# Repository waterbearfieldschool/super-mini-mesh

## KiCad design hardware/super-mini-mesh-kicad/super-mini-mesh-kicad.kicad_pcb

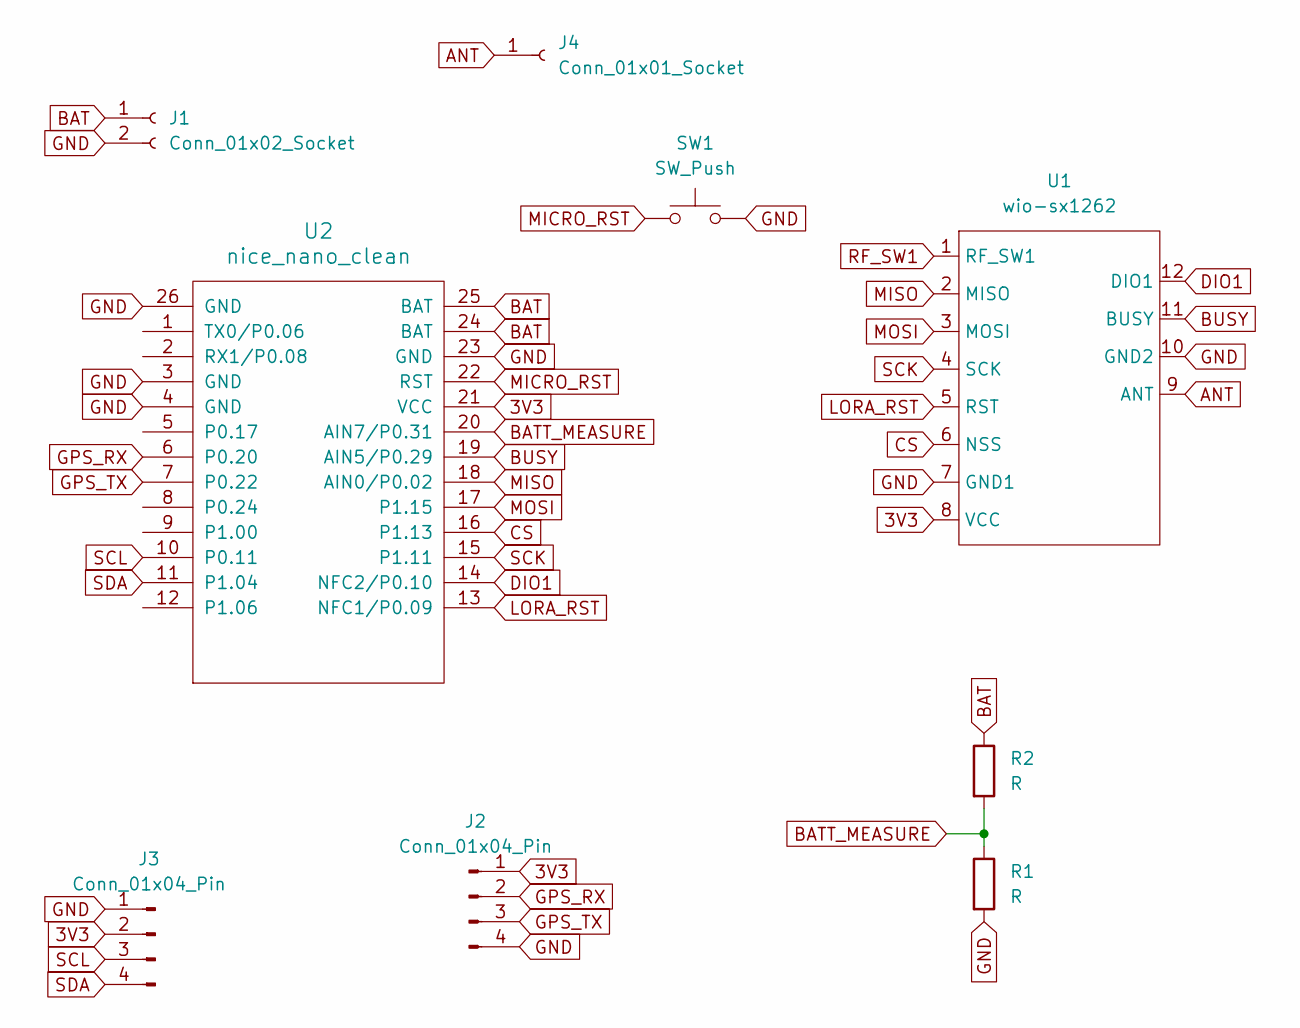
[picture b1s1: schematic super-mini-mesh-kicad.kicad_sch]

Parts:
J1: Conn_01x02_Socket; JST_PH_B2B-PH-K_1x02_P2.00mm_Vertical
J2, J3: Conn_01x04_Pin; PinHeader_1x04_P2.54mm_Vertical
J4: Conn_01x01_Socket; PinSocket_1x01_P2.54mm_Vertical
R1, R2: R; R_Axial_DIN0204_L3.6mm_D1.6mm_P1.90mm_Vertical
SW1: SW_Push; SW_PUSH_6mm
U1: wio-sx1262
U2: nice_nano_clean; nice_nano_cleanest

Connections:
3V3: J2.1, J3.2, U1.8 (VCC), U2.21 (VCC)
ANT: J4.1, U1.9 (ANT)
BAT: J1.1, R2.1, U2.24 (BAT), U2.25 (BAT)
BATT_MEASURE: R1.1, R2.2, U2.20 (AIN7/P0.31)
BUSY: U1.11 (BUSY), U2.19 (AIN5/P0.29)
CS: U1.6 (NSS), U2.16 (P1.13)
DIO1: U1.12 (DIO1), U2.14 (NFC2/P0.10)
GND: J1.2, J2.4, J3.1, R1.2, SW1.2, U1.7 (GND1), U1.10 (GND2), U2.3 (GND), U2.4 (GND), U2.23 (GND), U2.26 (GND)
GPS_RX: J2.2, U2.6 (P0.20)
GPS_TX: J2.3, U2.7 (P0.22)
LORA_RST: U1.5 (RST), U2.13 (NFC1/P0.09)
MICRO_RST: SW1.1, U2.22 (RST)
MISO: U1.2 (MISO), U2.18 (AIN0/P0.02)
MOSI: U1.3 (MOSI), U2.17 (P1.15)
RF_SW1: U1.1 (RF_SW1)
SCK: U1.4 (SCK), U2.15 (P1.11)
SCL: J3.3, U2.10 (P0.11)
SDA: J3.4, U2.11 (P1.04)

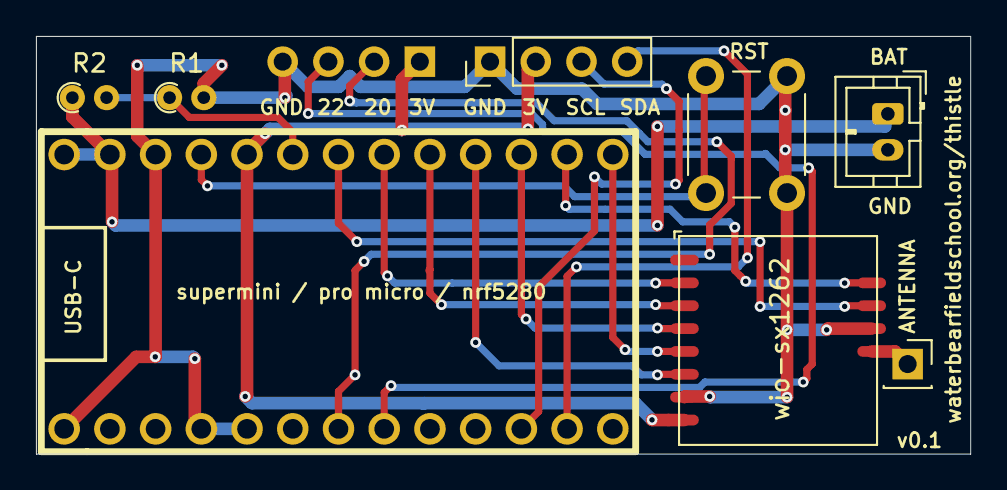
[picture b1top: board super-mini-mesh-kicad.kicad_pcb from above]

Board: 2 copper layers, 51.9 x 23.2 mm, 9 parts (1 on the bottom side), 17 nets.

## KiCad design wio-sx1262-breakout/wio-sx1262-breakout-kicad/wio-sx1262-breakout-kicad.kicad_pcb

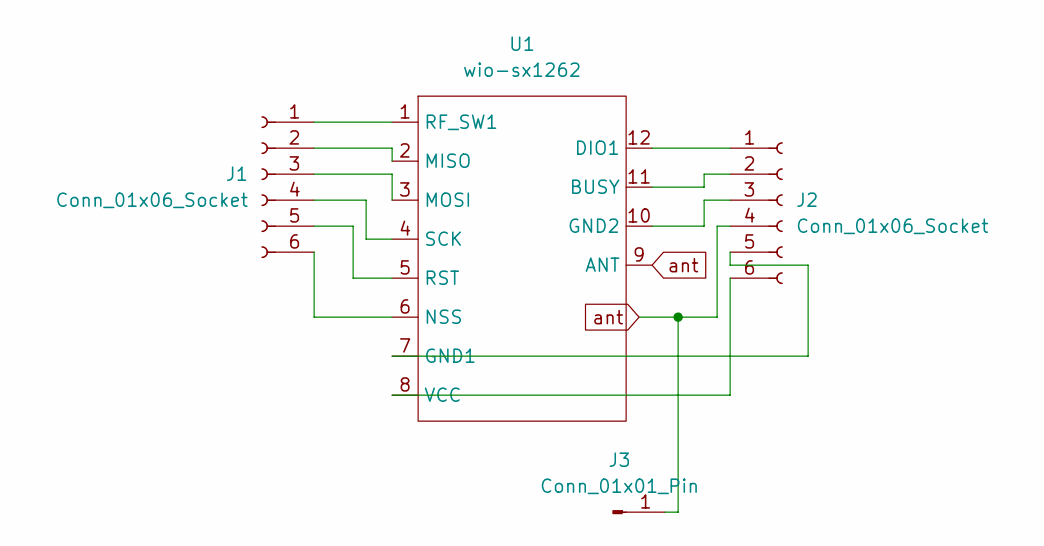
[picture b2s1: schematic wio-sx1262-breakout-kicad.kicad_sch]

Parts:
J1, J2: Conn_01x06_Socket; PinSocket_1x06_P2.54mm_Vertical
J3: Conn_01x01_Pin; PinSocket_1x01_P2.54mm_Vertical
U1: wio-sx1262

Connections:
unnamed: J1.1, U1.1 (RF_SW1)
unnamed: J1.2, U1.2 (MISO)
unnamed: J1.3, U1.3 (MOSI)
unnamed: J1.4, U1.4 (SCK)
unnamed: J1.5, U1.5 (RST)
unnamed: J1.6, U1.6 (NSS)
unnamed: J2.1, U1.12 (DIO1)
unnamed: J2.2, U1.11 (BUSY)
unnamed: J2.3, U1.10 (GND2)
unnamed: J2.5, U1.7 (GND1)
unnamed: J2.6, U1.8 (VCC)
ant: J2.4, J3.1, U1.9 (ANT)

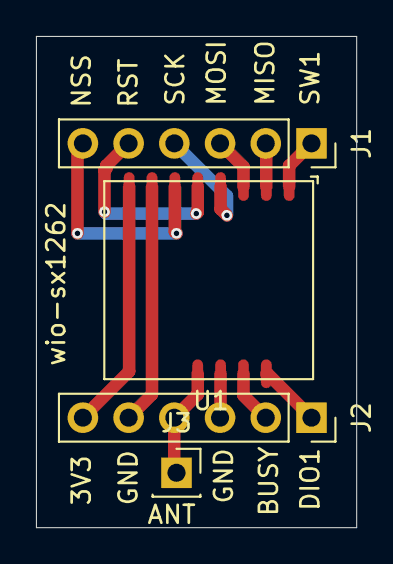
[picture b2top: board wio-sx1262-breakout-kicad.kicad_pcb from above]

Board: 2 copper layers, 17.8 x 27.3 mm, 4 parts (0 on the bottom side), 12 nets.
